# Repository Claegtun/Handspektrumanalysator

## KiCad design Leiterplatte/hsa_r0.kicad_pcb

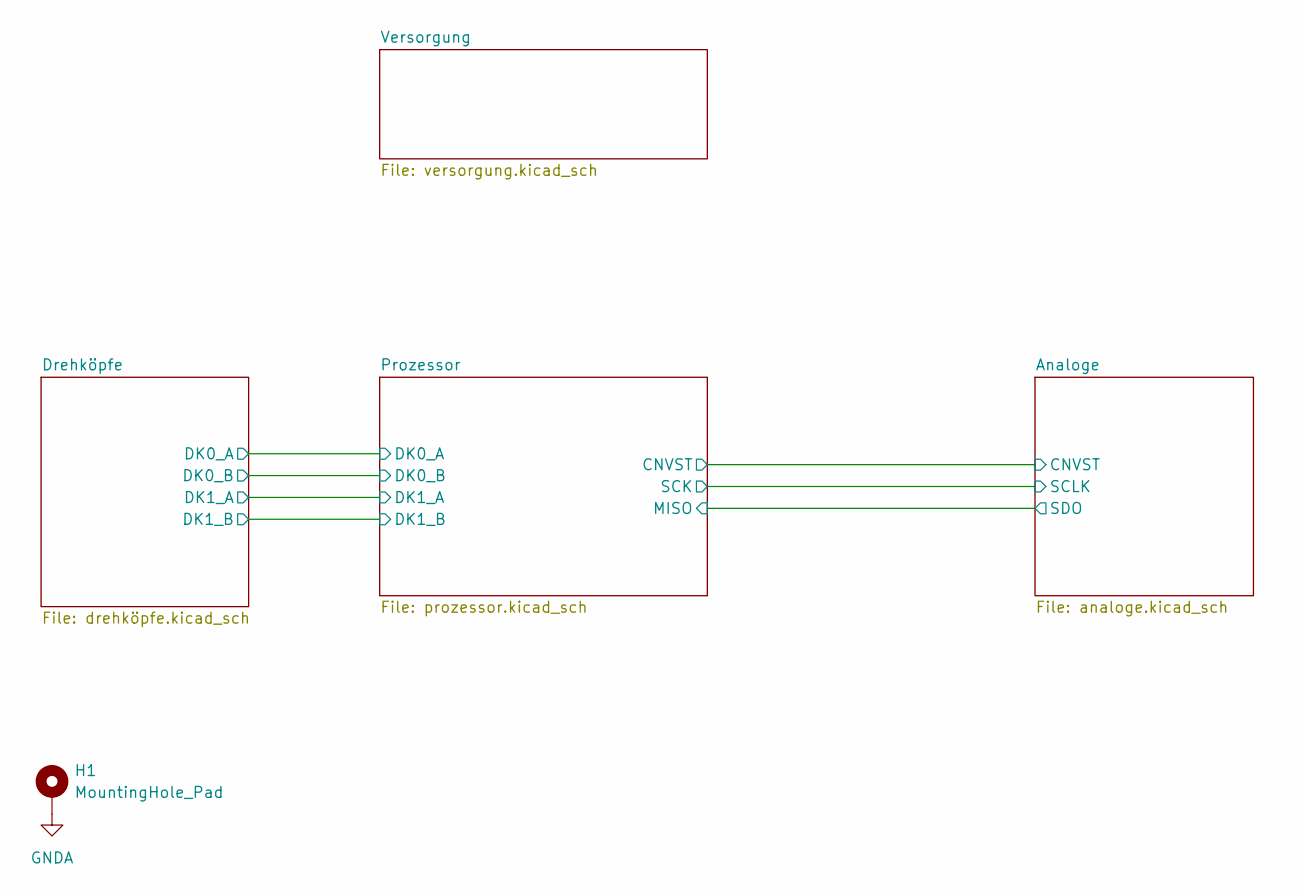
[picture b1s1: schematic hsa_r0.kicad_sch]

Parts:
H1: MountingHole_Pad; MountingHole_3.2mm_M3_ISO7380_Pad_TopBottom

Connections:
GNDA: H1.1; also elsewhere on the board

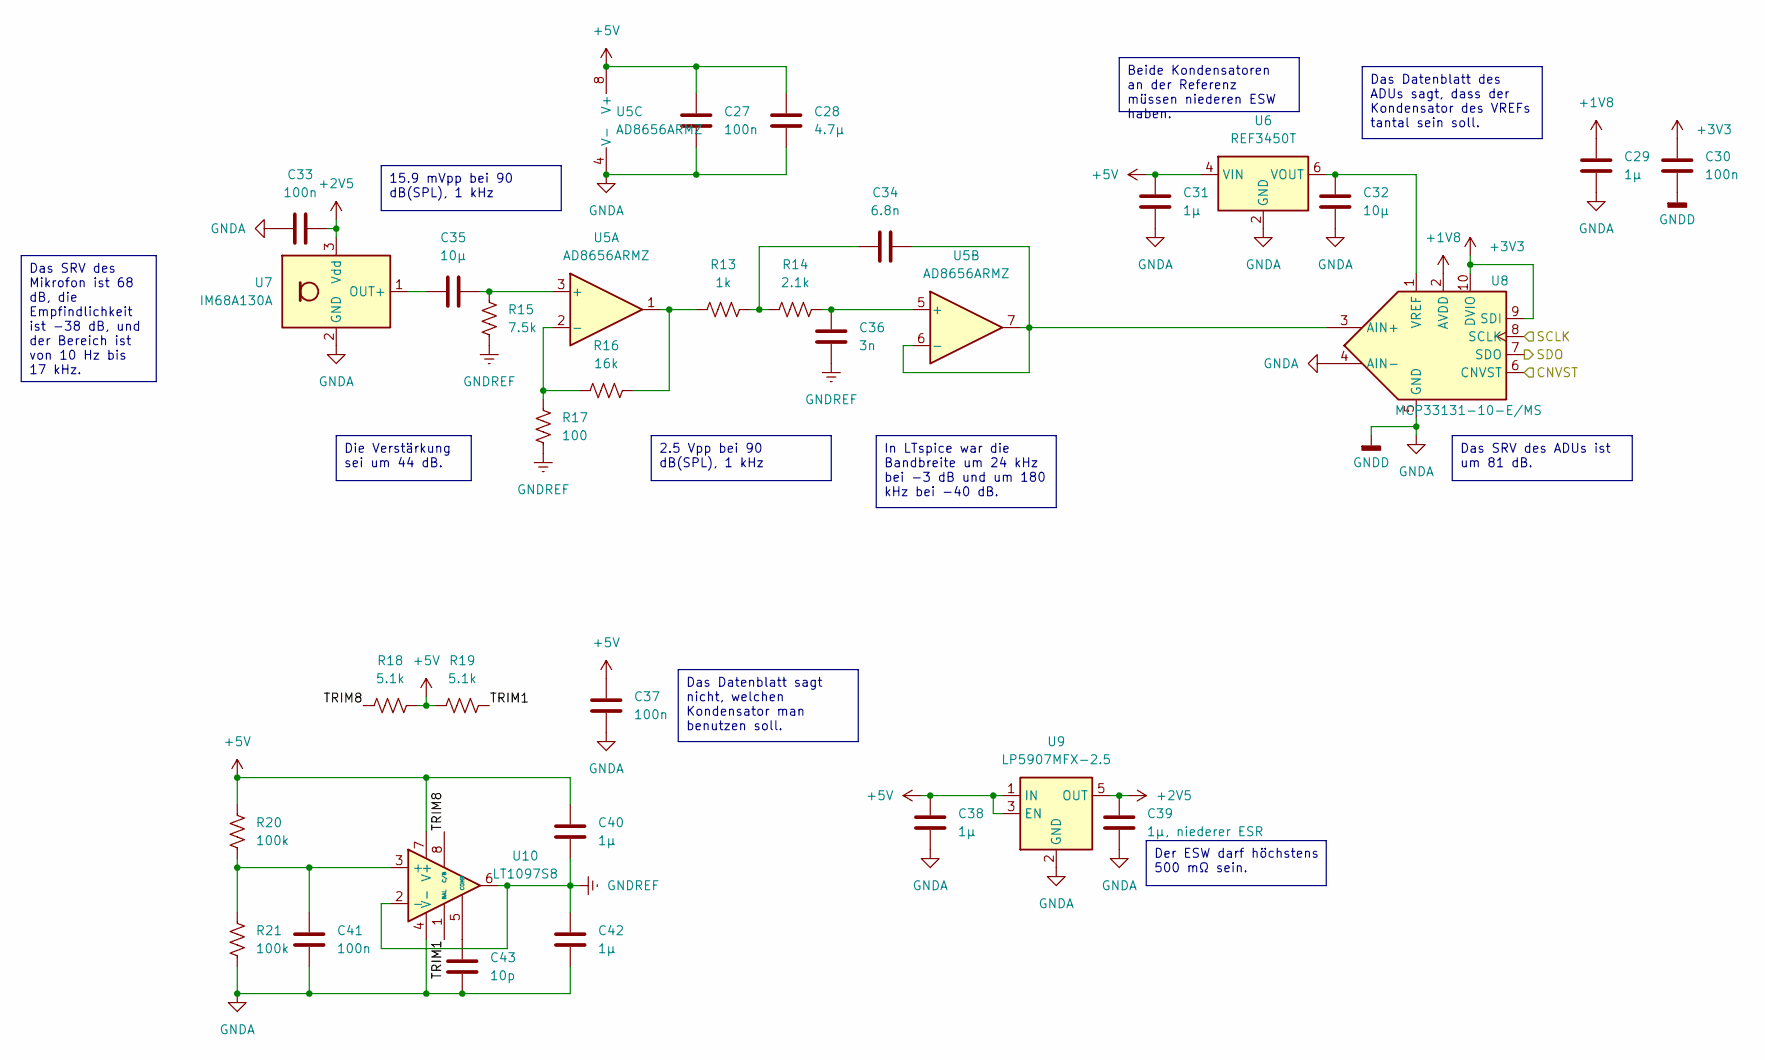
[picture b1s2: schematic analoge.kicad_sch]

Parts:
C27, C30, C33, C37, C41: 100n; C_0603_1608Metric
C28: 4.7μ; C_1206_3216Metric
C29, C40, C42: 1μ; C_0603_1608Metric
C31, C38: 1μ; C_1206_3216Metric
C32: 10μ; C_1206_3216Metric
C34: 6.8n; C_0603_1608Metric
C35: 10μ; C_0603_1608Metric
C36: 3n; C_0603_1608Metric
C39: 1μ, niederer ESR; C_1206_3216Metric
C43: 10p; C_0603_1608Metric
R13: 1k; R_0603_1608Metric
R14: 2.1k; R_0603_1608Metric
R15: 7.5k; R_0603_1608Metric
R16: 16k; R_0603_1608Metric
R17: 100; R_0603_1608Metric
R18, R19: 5.1k; R_0603_1608Metric
R20, R21: 100k; R_0603_1608Metric
U5: AD8656ARMZ; MSOP-8_3x3mm_P0.65mm
U6: REF3450T; SOT-23-6
U7: IM68A130A; IM68A130A_hand
U8: MCP33131-10-E/MS; MSOP-10_3x3mm_P0.5mm
U9: LP5907MFX-2.5; SOT-23-5
U10: LT1097S8; SOIC-8_3.9x4.9mm_P1.27mm

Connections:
+1V8: C29.1, U8.2 (AVDD); also elsewhere on the board
+2V5: C33.2, C39.1, U7.3 (Vdd), U9.5 (OUT)
+3V3: C30.1, U8.9 (SDI), U8.10 (DVIO); also elsewhere on the board
+5V: C27.1, C28.1, C31.1, C37.1, C38.1, C40.1, R18.2, R19.1, R20.1, U5.8 (V+), U6.4 (VIN), U9.1 (IN), U9.3 (EN), U10.7 (V+); also elsewhere on the board
/Analoge/TRIM1: R19.2, U10.1 (BAL)
/Analoge/TRIM8: R18.1, U10.8 (C/B)
/Prozessor/AADU_CNVST: U8.6 (CNVST); also elsewhere on the board
/Prozessor/AADU_MISO: U8.7 (SDO); also elsewhere on the board
/Prozessor/AADU_SCK: U8.8 (SCLK); also elsewhere on the board
GNDA: C27.2, C28.2, C29.2, C30.2, C31.2, C32.2, C33.1, C37.2, C38.2, C39.2, C41.2, C42.2, C43.2, R21.2, U5.4 (V-), U6.2 (GND), U7.2 (GND), U7.4 (GND), U8.4 (AIN-), U8.5 (GND), U9.2 (GND), U10.4 (V-); also elsewhere on the board
GNDREF: C36.1, C40.2, C42.1, R15.1, R17.1, U10.2 (-), U10.6
unnamed: C34.1, R13.2, R14.1
unnamed: R13.1, R16.2, U5.1
unnamed: C35.2, R15.2, U5.3 (+)
unnamed: R16.1, R17.2, U5.2 (-)
unnamed: C36.2, R14.2, U5.5 (+)
unnamed: C34.2, U5.6 (-), U5.7, U8.3 (AIN+)
unnamed: C32.1, U6.6 (VOUT), U8.1 (VREF)
unnamed: C35.1, U7.1 (OUT+)
unnamed: C41.1, R20.2, R21.1, U10.3 (+)
unnamed: C43.1, U10.5 (COMP)

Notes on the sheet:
Das Datenblatt des ADUs sagt, dass der Kondensator des VREFs tantal sein soll.
15.9 mVpp bei 90 dB(SPL), 1 kHz
Das SRV des Mikrofon ist 68 dB, die Empfindlichkeit ist -38 dB, und der Bereich ist von 10 Hz bis 17 kHz.
Die Verstärkung sei um 44 dB.
In LTspice war die Bandbreite um 24 kHz bei -3 dB und um 180 kHz bei -40 dB.
Das SRV des ADUs ist um 81 dB.
Beide Kondensatoren an der Referenz müssen niederen ESW haben.
2.5 Vpp bei 90 dB(SPL), 1 kHz
Der ESW darf höchstens 500 mΩ sein.
Das Datenblatt sagt nicht, welchen Kondensator man benutzen soll.

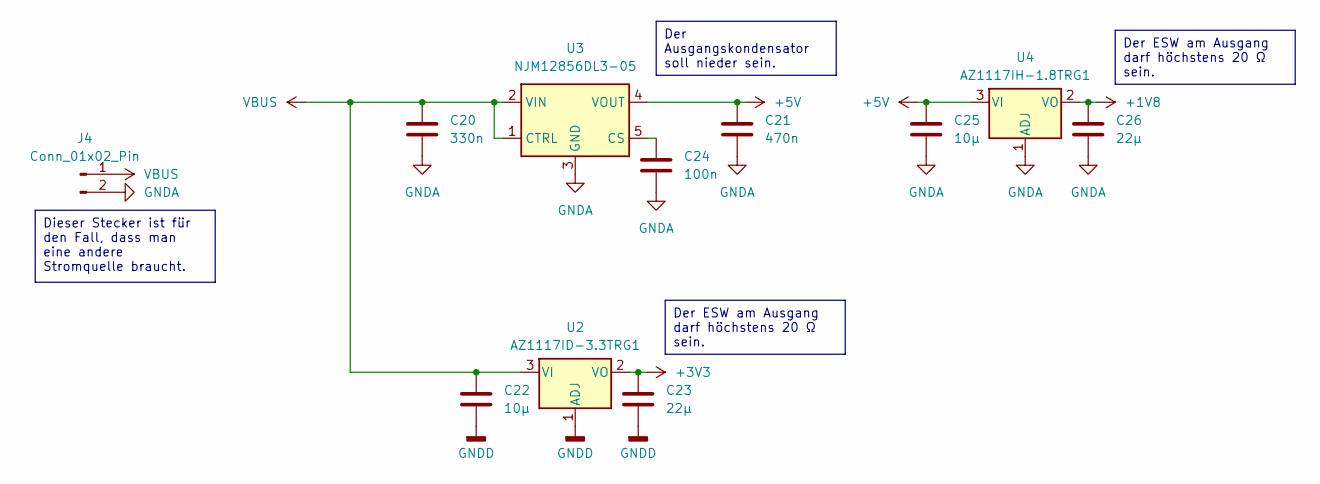
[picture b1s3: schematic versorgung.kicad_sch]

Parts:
C20: 330n; C_1206_3216Metric
C21: 470n; C_1206_3216Metric
C22, C25: 10μ; C_1206_3216Metric
C23, C26: 22μ; C_1206_3216Metric
C24: 100n; C_0603_1608Metric
J4: Conn_01x02_Pin; PinHeader_1x02_P2.54mm_Vertical
U2: AZ1117ID-3.3TRG1; TO-252-2
U3: NJM12856DL3-05; TO-252-5_TabPin3
U4: AZ1117IH-1.8TRG1; SOT-223-3_TabPin2

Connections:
+1V8: C26.1, U4.2 (VO); also elsewhere on the board
+3V3: C23.1, U2.2 (VO); also elsewhere on the board
+5V: C21.1, C25.1, U3.4 (VOUT), U4.3 (VI); also elsewhere on the board
GNDA: C20.2, C21.2, C22.2, C23.2, C24.2, C25.2, C26.2, J4.2, U2.1 (ADJ), U3.3 (GND), U3.7 (GND), U4.1 (ADJ); also elsewhere on the board
unnamed: C24.1, U3.5 (CS)
VBUS: C20.1, C22.1, J4.1, U2.3 (VI), U3.1 (CTRL), U3.2 (VIN); also elsewhere on the board

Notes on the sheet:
Der Ausgangskondensator soll nieder sein.
Der ESW am Ausgang darf höchstens 20 Ω sein.
Dieser Stecker ist für den Fall, dass man eine andere Stromquelle braucht.

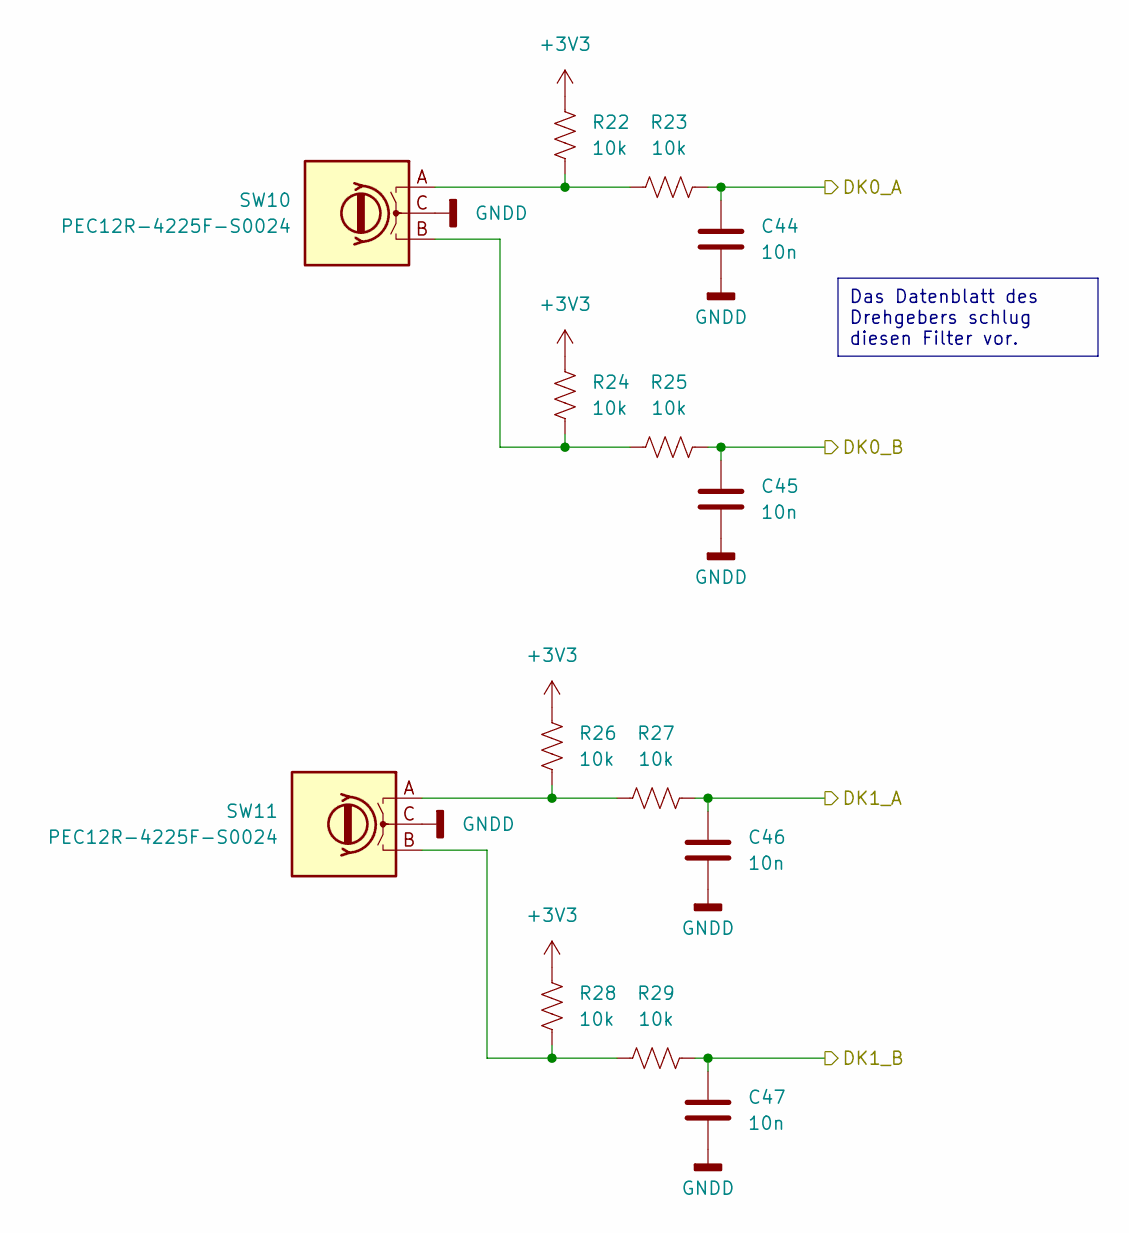
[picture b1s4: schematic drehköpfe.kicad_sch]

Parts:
C44, C45, C46, C47: 10n; C_0603_1608Metric
R22, R23, R24, R25, R26, R27, R28, R29: 10k; R_0603_1608Metric
SW10, SW11: PEC12R-4225F-S0024; RotaryEncoder_Bourns_Horizontal_PEC09-2xxxF-Nxxxx

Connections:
+3V3: R22.2, R24.2, R26.2, R28.2; also elsewhere on the board
/Prozessor/DK0_A: C44.1, R23.1; also elsewhere on the board
/Prozessor/DK0_B: C45.1, R25.1; also elsewhere on the board
/Prozessor/DK1_A: C46.1, R27.1; also elsewhere on the board
/Prozessor/DK1_B: C47.1, R29.1; also elsewhere on the board
GNDA: C44.2, C45.2, C46.2, C47.2, SW10.C, SW11.C; also elsewhere on the board
unnamed: R22.1, R23.2, SW10.A
unnamed: R24.1, R25.2, SW10.B
unnamed: R26.1, R27.2, SW11.A
unnamed: R28.1, R29.2, SW11.B

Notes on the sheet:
Das Datenblatt des Drehgebers schlug diesen Filter vor.

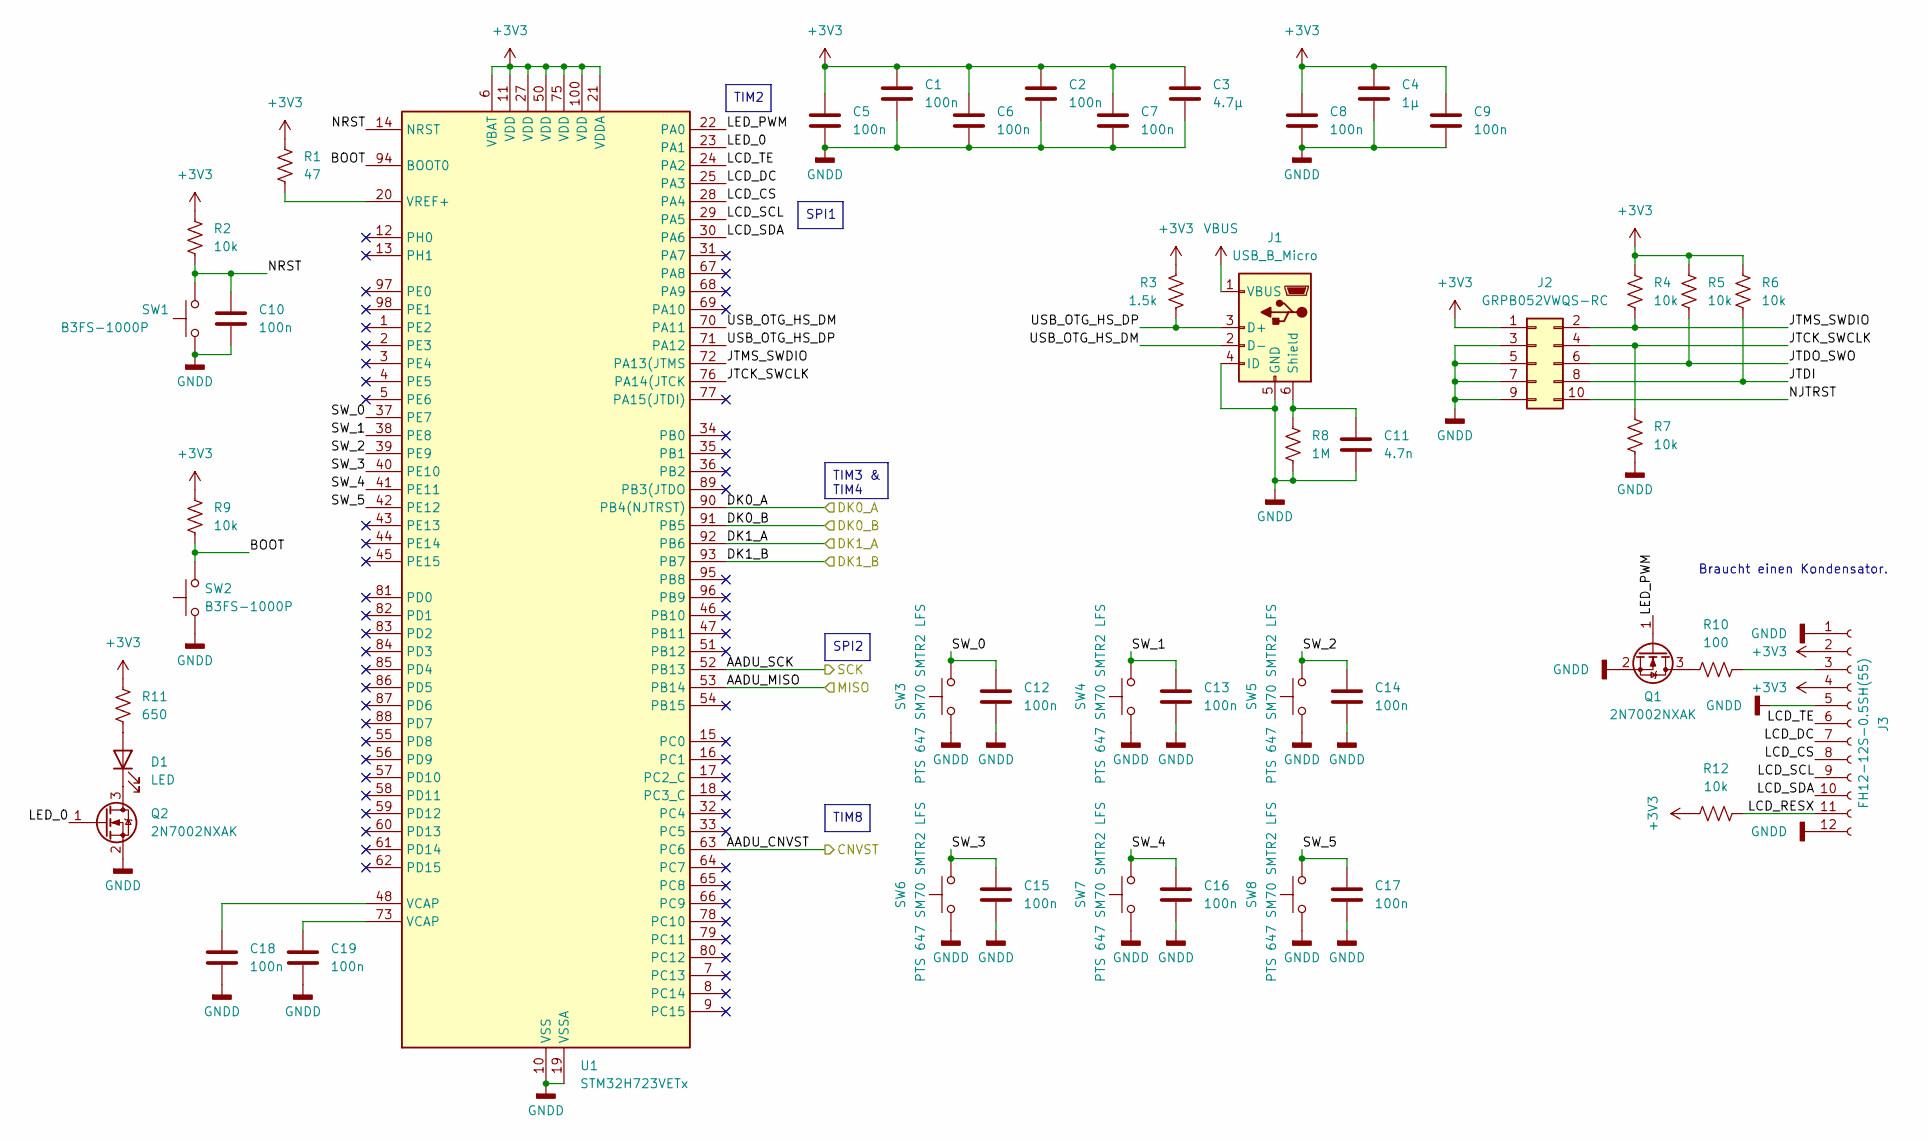
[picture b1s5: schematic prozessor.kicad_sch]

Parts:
C1, C2, C5, C6, C7, C8, C9, C10, C12, C13, C14, C15, C16, C17, C18, C19: 100n; C_0603_1608Metric
C3: 4.7μ; C_0805_2012Metric
C4: 1μ; C_0805_2012Metric
C11: 4.7n; C_0603_1608Metric
D1: LED; LED_0805_2012Metric
J1: USB_B_Micro; USB_Micro-B_Amphenol_10118193-0001LF_Horizontal
J2: GRPB052VWQS-RC; PinHeader_2x05_P1.27mm_Vertical_SMD
J3: FH12-12S-0.5SH(55); Hirose_FH12-12S-0.5SH_1x12-1MP_P0.50mm_Horizontal
Q1, Q2: 2N7002NXAK; SOT-23
R1: 47; R_0603_1608Metric
R2, R4, R5, R6, R7, R9, R12: 10k; R_0603_1608Metric
R3: 1.5k; R_0603_1608Metric
R8: 1M; R_0603_1608Metric
R10: 100; R_0603_1608Metric
R11: 650; R_0603_1608Metric
SW1, SW2: B3FS-1000P; häufige_kurzhubtaster
SW3, SW4, SW5, SW6, SW7, SW8: PTS 647 SM70 SMTR2 LFS; häufige_kurzhubtaster
U1: STM32H723VETx; LQFP-100_14x14mm_P0.5mm

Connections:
+3V3: C1.1, C2.1, C3.1, C4.1, C5.1, C6.1, C7.1, C8.1, C9.1, J2.1, J3.2, J3.4, R1.2, R2.1, R3.1, R4.1, R5.1, R6.1, R9.1, R11.2, R12.1, U1.6 (VBAT), U1.11 (VDD), U1.21 (VDDA), U1.27 (VDD), U1.50 (VDD), U1.75 (VDD), U1.100 (VDD); also elsewhere on the board
/Prozessor/AADU_CNVST: U1.63 (PC6); also elsewhere on the board
/Prozessor/AADU_MISO: U1.53 (PB14); also elsewhere on the board
/Prozessor/AADU_SCK: U1.52 (PB13); also elsewhere on the board
/Prozessor/BOOT: R9.2, SW2.2, U1.94 (BOOT0)
/Prozessor/DK0_A: U1.90 (PB4(NJTRST)); also elsewhere on the board
/Prozessor/DK0_B: U1.91 (PB5); also elsewhere on the board
/Prozessor/DK1_A: U1.92 (PB6); also elsewhere on the board
/Prozessor/DK1_B: U1.93 (PB7); also elsewhere on the board
/Prozessor/JTCK_SWCLK: J2.4, R7.1, U1.76 (PA14(JTCK)
/Prozessor/JTDI: J2.8, R6.2
/Prozessor/JTDO_SWO: J2.6, R5.2
/Prozessor/JTMS_SWDIO: J2.2, R4.2, U1.72 (PA13(JTMS)
/Prozessor/LCD_CS: J3.8, U1.28 (PA4)
/Prozessor/LCD_DC: J3.7, U1.25 (PA3)
/Prozessor/LCD_RESX: J3.11, R12.2
/Prozessor/LCD_SCL: J3.9, U1.29 (PA5)
/Prozessor/LCD_SDA: J3.10, U1.30 (PA6)
/Prozessor/LCD_TE: J3.6, U1.24 (PA2)
/Prozessor/LED_0: Q2.1 (G), U1.23 (PA1)
/Prozessor/LED_PWM: Q1.1 (G), U1.22 (PA0)
/Prozessor/NJTRST: J2.10
/Prozessor/NRST: C10.1, R2.2, SW1.2, U1.14 (NRST)
/Prozessor/SW_0: C12.1, SW3.1, U1.37 (PE7)
/Prozessor/SW_1: C13.1, SW4.1, U1.38 (PE8)
/Prozessor/SW_2: C14.1, SW5.1, U1.39 (PE9)
/Prozessor/SW_3: C15.1, SW6.1, U1.40 (PE10)
/Prozessor/SW_4: C16.1, SW7.1, U1.41 (PE11)
/Prozessor/SW_5: C17.1, SW8.1, U1.42 (PE12)
/Prozessor/USB_OTG_HS_DM: J1.2 (D-), U1.70 (PA11)
/Prozessor/USB_OTG_HS_DP: J1.3 (D+), R3.2, U1.71 (PA12)
GNDA: C1.2, C2.2, C3.2, C4.2, C5.2, C6.2, C7.2, C8.2, C9.2, C10.2, C11.2, C12.2, C13.2, C14.2, C15.2, C16.2, C17.2, C18.1, C19.2, J1.4 (ID), J1.5 (GND), J2.3, J2.5, J2.7, J2.9, J3.1, J3.5, J3.12, Q1.2 (S), Q2.2 (S), R7.2, R8.2, SW1.1, SW2.1, SW3.2, SW4.2, SW5.2, SW6.2, SW7.2, SW8.2, U1.10 (VSS), U1.19 (VSSA), U1.26 (VSS), U1.49 (VSS), U1.74 (VSS), U1.99 (VSS); also elsewhere on the board
unnamed: C18.2, U1.48 (VCAP)
unnamed: C19.1, U1.73 (VCAP)
unnamed: D1.2 (A), R11.1
unnamed: D1.1 (K), Q2.3 (D)
unnamed: C11.1, J1.6 (Shield), R8.1
unnamed: J3.3, R10.2
unnamed: Q1.3 (D), R10.1
unnamed: R1.1, U1.20 (VREF+)
VBUS: J1.1 (VBUS); also elsewhere on the board

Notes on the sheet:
SPI2
TIM2
TIM3 & TIM4
TIM8
SPI1
Braucht einen Kondensator.

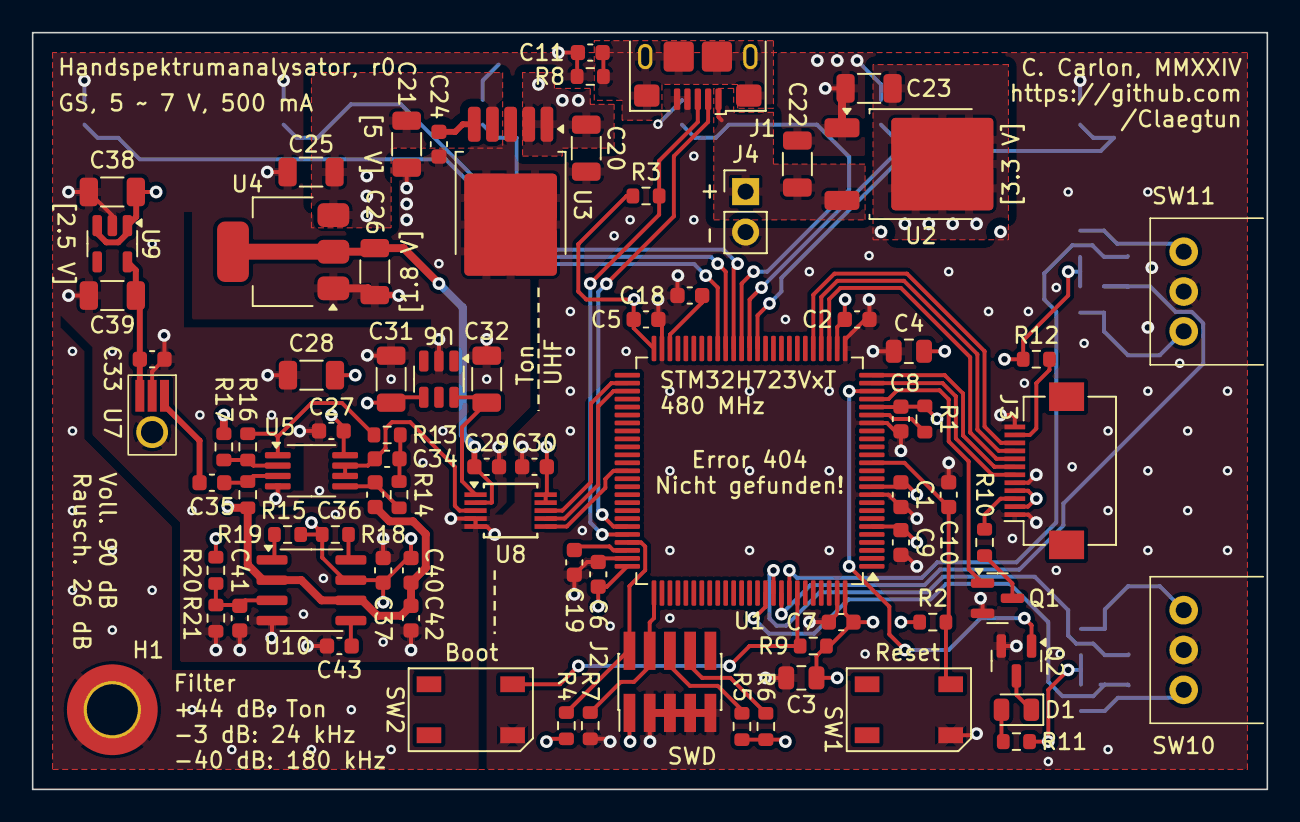
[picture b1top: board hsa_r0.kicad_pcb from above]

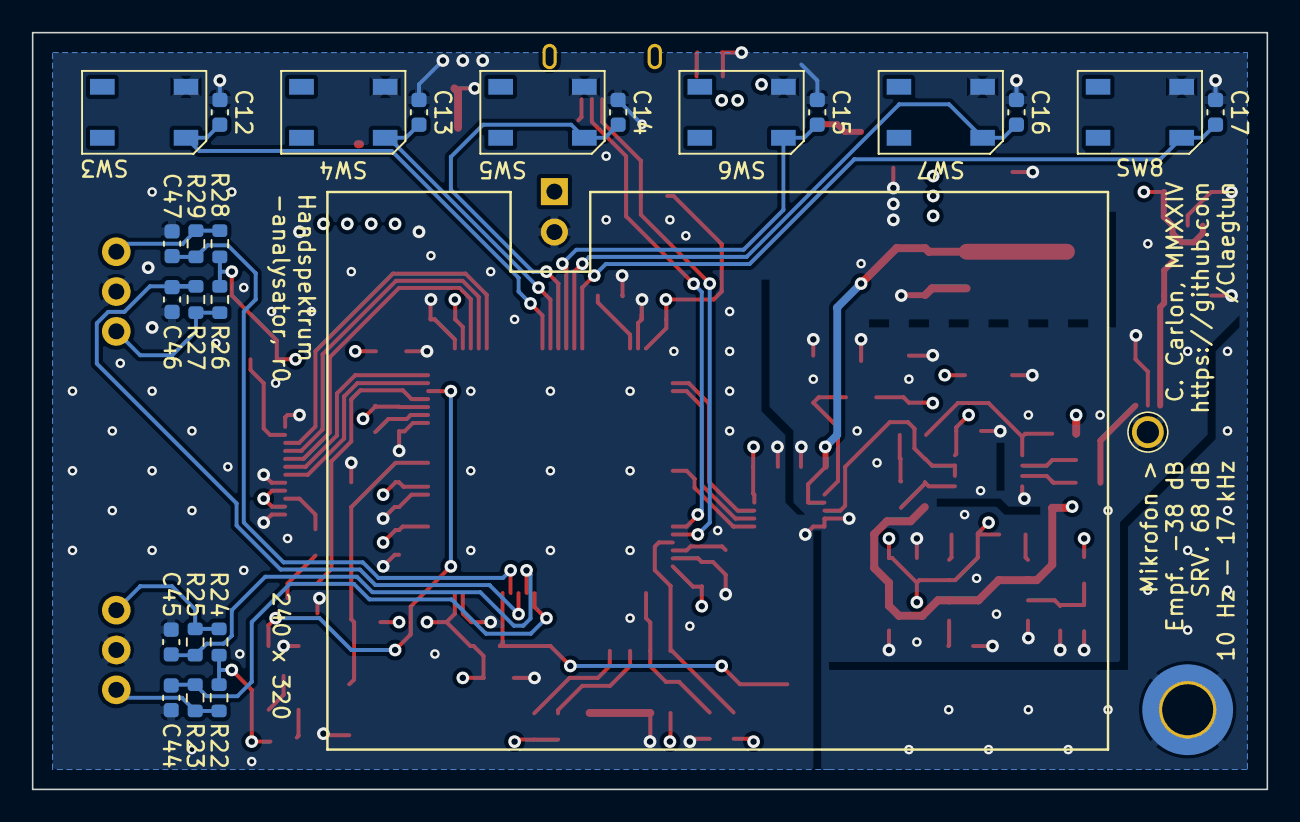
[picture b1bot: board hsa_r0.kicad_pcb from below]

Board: 4 copper layers, 77.5 x 47.5 mm, 104 parts (24 on the bottom side), 61 nets.

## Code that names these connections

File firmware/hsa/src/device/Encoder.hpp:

#include "stm32h7xx_hal.h"
#include "peripheral/register.hpp"
#include <array>
#include <cstdint>

namespace device {

    /// @brief  Drehkopf / Rotary Encoder
    /// @tparam K whether the encoder is the top one (0) or the bottom (1).
    template<uint8_t K>
    class Encoder {
        public:

            /// @brief  Constructs the object.
            Encoder() {
                // ~~~ Timer ~~~

                // This timer decodes the quadrature signal from the rotary encoder. It counts 
                // either up or down depending on the quadrature phase.

                if constexpr (K == 0) {
                    // Choose TIM3 since it has pins bound to the encoder.
                    tim = TIM3;

                    // Turn the clock on for TIM3.
                    SET_BIT(RCC->APB1LENR, 1);
                } else {
                    // Choose TIM4 since it has pins bound to the encoder.
                    tim = TIM4;

                    // Turn the clock on for TIM4.
                    SET_BIT(RCC->APB1LENR, 2);
                }

                // Set the timer up.
                CLEAR_BIT(tim->CR1, 4);                    // Count upwards.
                CLEAR_BIT(tim->CR1, 3);                    // Keep counting.
                CLEAR_BIT(tim->CR2, 7);                    // Bind CH1 to T1.
                WRITE_FIELD(tim->SMCR, 0, 0x7, 0x03);      // Set Encoder mode 3.
                WRITE_FIELD(tim->CCMR1, 0, 0b11, 0b01);    // Set CH1 to an input.
                WRITE_FIELD(tim->CCMR1, 8, 0b11, 0b01);    // Set CH2 to an input.

                // CH2
                CLEAR_BIT(tim->CCER, 7);                   // Count on the rising edge.
                CLEAR_BIT(tim->CCER, 5);                   // Set the polarity to active high.
                // CH1
                CLEAR_BIT(tim->CCER, 3);                   // Count on the rising edge.
                CLEAR_BIT(tim->CCER, 1);                   // Set the polarity to active high.

                tim->PSC = 4;     // Set the prescaler.
                tim->ARR = 255;   // Set the period.
                tim->CCR1 = 128;  // Set the duty-cycle.

                if constexpr (K == 0) {
                    // Set four pins up as inputs.
                    WRITE_FIELD(GPIOB->MODER, 4*2, 0b11, 0b10); // Set PB4 as an alternate function.
                    WRITE_FIELD(GPIOB->AFR[0], 4*4, 0xF, 0x2);  // Use Alternate Function 2.
                    WRITE_FIELD(GPIOB->MODER, 5*2, 0b11, 0b10); // Set PB5 as an alternate function.
                    WRITE_FIELD(GPIOB->AFR[0], 5*4, 0xF, 0x2);  // Use Alternate Function 2.
                } else {
                    // Set four pins up as inputs.
                    WRITE_FIELD(GPIOB->MODER, 6*2, 0b11, 0b10); // Set PB6 as an alternate function.
                    WRITE_FIELD(GPIOB->AFR[0], 6*4, 0xF, 0x2);  // Use Alternate Function 2.
                    WRITE_FIELD(GPIOB->MODER, 7*2, 0b11, 0b10); // Set PB7 as an alternate function.
                    WRITE_FIELD(GPIOB->AFR[0], 7*4, 0xF, 0x2);  // Use Alternate Function 2.
                }

                SET_BIT(tim->CR1, 0); // Begin counting.
            }

            /// @brief  Gets the current value of the encoder.
            /// @return The count register of the timer.
            const uint8_t get_count() const {
                count = tim->CNT;
                return count;
            }

            /// @brief  Gets the shift of the encoder.
            /// @return The shift in the timer's counter.
            const int8_t get_shift() {
                int8_t shift = int8_t(count) - int8_t(tim->CNT);
                count = tim->CNT;
                return shift;
            }

        private:
            /// @brief  A reference to the peripheral timer.
            /// @note   A better approach may be to use a reference instead.
            TIM_TypeDef* tim = TIM3;
            /// @brief  A copy of the timer's count.
            uint8_t count = 0;
    };

} // namespace device

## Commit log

2024-08-11 Erste Festschreibung
2024-08-25 Leitete und beendete am meisten die Leiterplatte.
2025-02-14 Lieber Gott helfe mir.
2025-10-24 längst
